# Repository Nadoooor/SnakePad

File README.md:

# SnakePad
A little macro-pad in a snake shape 👀👀👀👀🐍
## The Schematic:

## The PCB:

## The 3D PCB: 

## The CAD:

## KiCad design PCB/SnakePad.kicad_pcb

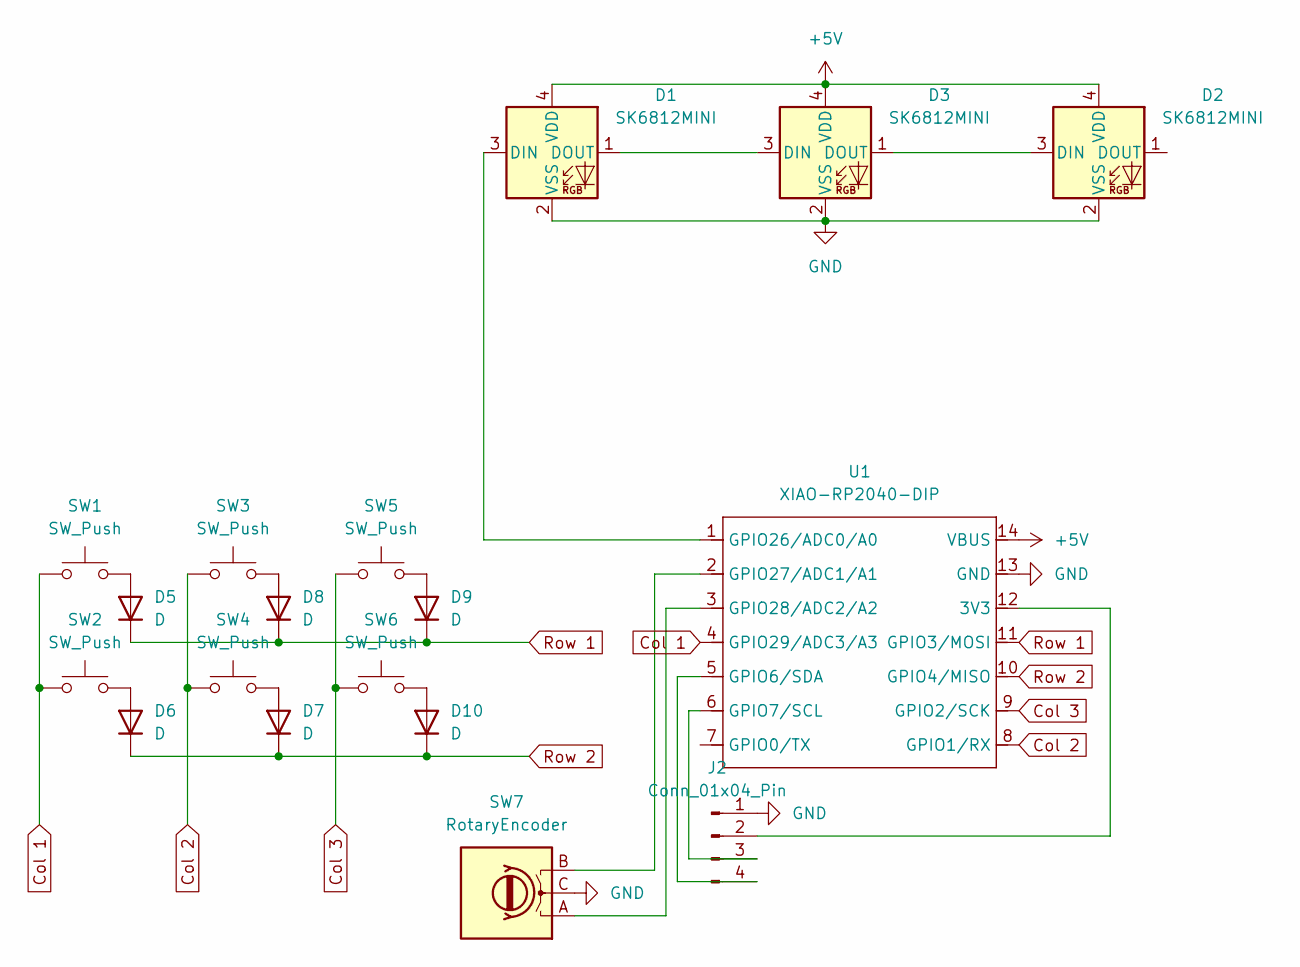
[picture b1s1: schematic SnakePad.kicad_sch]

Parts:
D1, D2, D3: SK6812MINI; LED_SK6812MINI_PLCC4_3.5x3.5mm_P1.75mm
D5, D6, D7, D8, D9, D10: D; D_DO-35_SOD27_P7.62mm_Horizontal
J2: Conn_01x04_Pin; SSD1306_0.96_Oled
SW1, SW2, SW3, SW4, SW5, SW6: SW_Push; SW_Cherry_MX_1.00u_PCB
SW7: RotaryEncoder; RotaryEncoder_Alps_EC11E-Switch_Vertical_H20mm_CircularMoun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
U1: XIAO-RP2040-DIP; Seeed_XIAO_RP2040

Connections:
+5V: D1.4 (VDD), D2.4 (VDD), D3.4 (VDD), U1.14 (VBUS)
Col 1: SW1.1, SW2.1, U1.4 (GPIO29/ADC3/A3)
Col 2: SW3.1, SW4.1, U1.8 (GPIO1/RX)
Col 3: SW5.1, SW6.1, U1.9 (GPIO2/SCK)
GND: D1.2 (VSS), D2.2 (VSS), D3.2 (VSS), J2.1, SW7.C, U1.13 (GND)
unnamed: D1.3 (DIN), U1.1 (GPIO26/ADC0/A0)
unnamed: D1.1 (DOUT), D3.3 (DIN)
unnamed: D2.3 (DIN), D3.1 (DOUT)
unnamed: D5.2 (A), SW1.2
unnamed: D6.2 (A), SW2.2
unnamed: D7.2 (A), SW4.2
unnamed: D8.2 (A), SW3.2
unnamed: D9.2 (A), SW5.2
unnamed: D10.2 (A), SW6.2
unnamed: J2.2, U1.12 (3V3)
unnamed: J2.3, U1.6 (GPIO7/SCL)
unnamed: J2.4, U1.5 (GPIO6/SDA)
unnamed: SW7.B, U1.2 (GPIO27/ADC1/A1)
unnamed: SW7.A, U1.3 (GPIO28/ADC2/A2)
Row 1: D5.1 (K), D8.1 (K), D9.1 (K), U1.11 (GPIO3/MOSI)
Row 2: D6.1 (K), D7.1 (K), D10.1 (K), U1.10 (GPIO4/MISO)

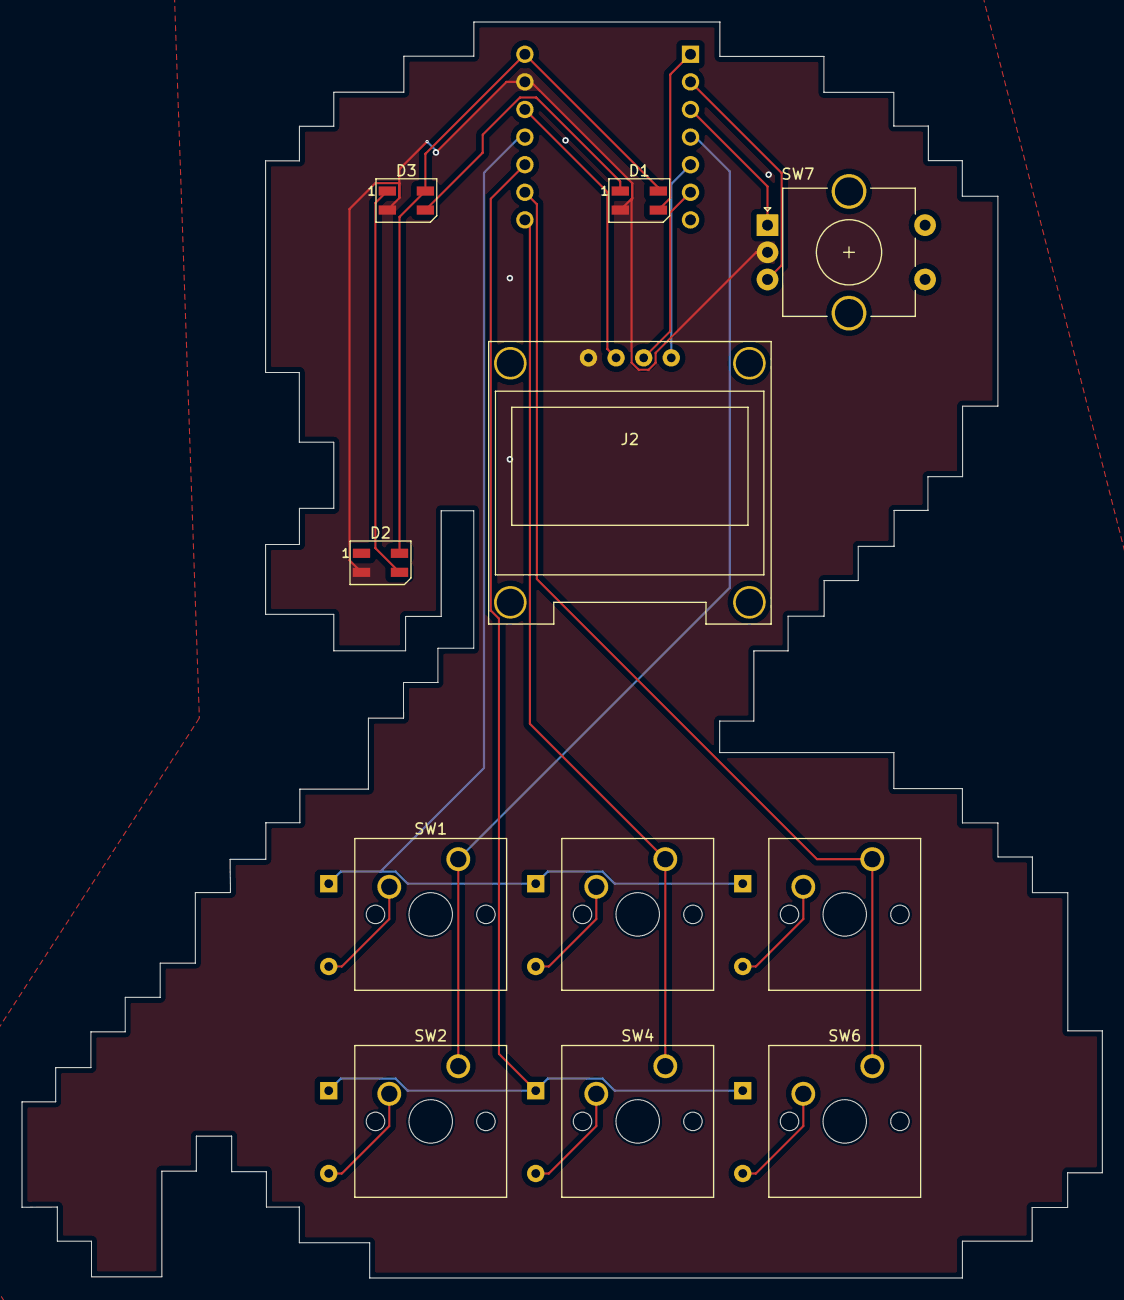
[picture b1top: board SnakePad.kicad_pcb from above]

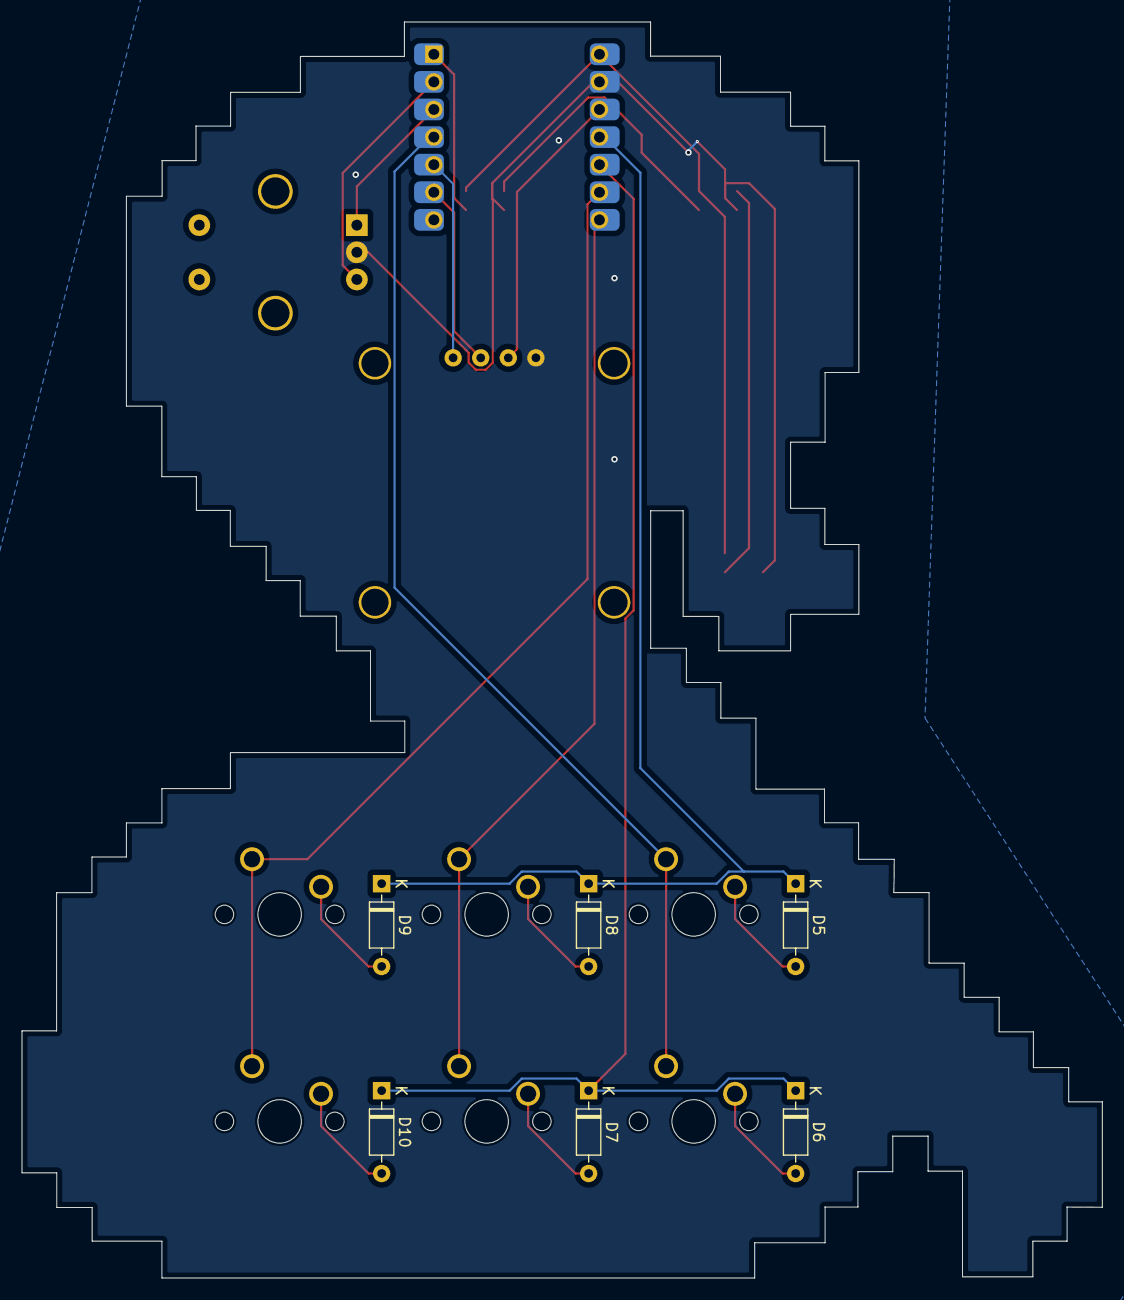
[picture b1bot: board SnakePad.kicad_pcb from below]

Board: 2 copper layers, 99.4 x 115.6 mm, 18 parts (7 on the bottom side), 21 nets.

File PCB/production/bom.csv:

Designator,Footprint,Quantity,Value,LCSC Part #
"D1, D2, D3",LED_SK6812MINI_PLCC4_3.5x3.5mm_P1.75mm,3,SK6812MINI,
"D10, D5, D6, D7, D8, D9",D_DO-35_SOD27_P7.62mm_Horizontal,6,D,
J2,SSD1306_0.96_Oled,1,Conn_01x04_Pin,
"SW1, SW2, SW3, SW4, SW5, SW6",SW_Cherry_MX_1.00u_PCB,6,SW_Push,
SW7,RotaryEncoder_Alps_EC11E-Switch_Vertical_H20mm_CircularMountingHoles,1,RotaryEncoder,
U1,Seeed_XIAO_RP2040,1,XIAO-RP2040-DIP,

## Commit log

2025-06-02 Add The Project
    Forgot to work on the project while iam on the repo and worked on it on a local folder 👀
2025-06-03 Adding the Firmware
